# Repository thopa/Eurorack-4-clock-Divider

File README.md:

# Eurorack-4-clock-Divider
4 channel Eurorack Clock Divider, using Arduino NANO, and modified code from the Ardcore

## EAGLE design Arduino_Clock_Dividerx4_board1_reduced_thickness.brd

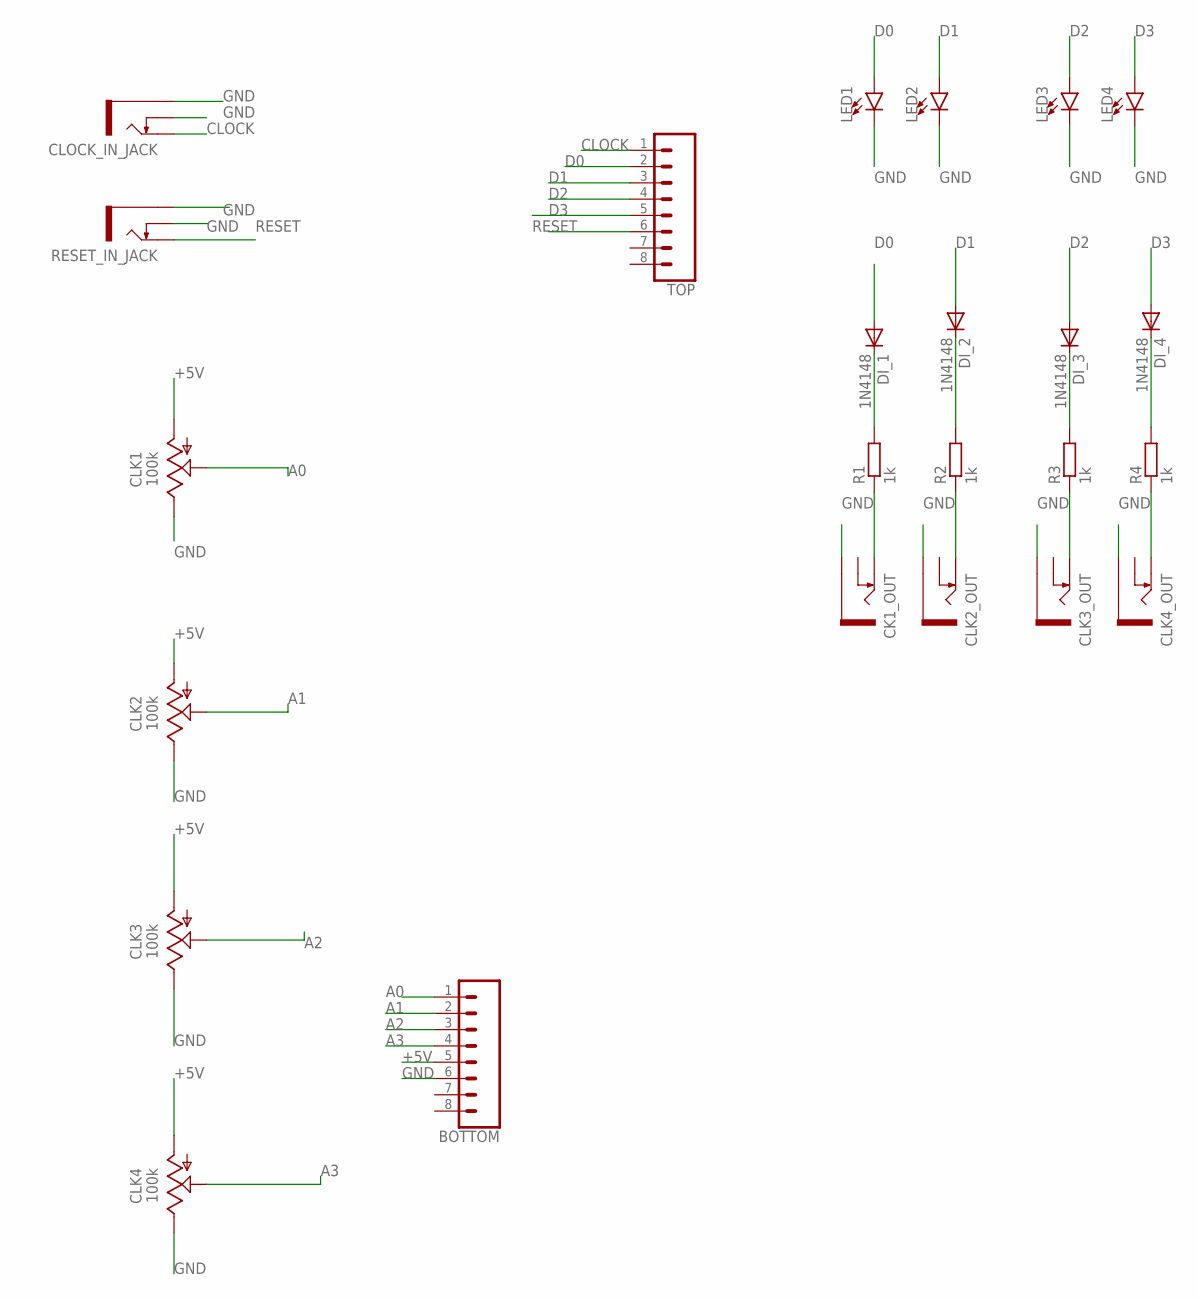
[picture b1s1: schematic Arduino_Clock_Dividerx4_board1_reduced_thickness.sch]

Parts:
BOTTOM: CONN_08LONGPADS; 1X08_LONGPADS
CK1_OUT: THONKICONNNEW; WQP-PJ301M-12_JACK
CLK1, CLK2, CLK3, CLK4: 100k; 9MM_SNAP-IN_POT
CLK2_OUT, CLK3_OUT, CLK4_OUT: THONKICONNNEW; WQP-PJ301M-12_JACK
CLOCK_IN_JACK: THONKICONNNEW; WQP-PJ301M-12_JACK
DI_1, DI_2, DI_3, DI_4: 1N4148; DO35-7
LED1, LED2, LED3, LED4: LED3MM; LED_3MM
R1, R2, R3, R4: 1k; 7MM_RESISTOR
RESET_IN_JACK: THONKICONNNEW; WQP-PJ301M-12_JACK
TOP: CONN_08LONGPADS; 1X08_LONGPADS

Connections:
+5V: BOTTOM.5, CLK1.1 (A), CLK2.1 (A), CLK3.1 (A), CLK4.1 (A)
A0: BOTTOM.1, CLK1.2 (S)
A1: BOTTOM.2, CLK2.2 (S)
A2: BOTTOM.3, CLK3.2 (S)
A3: BOTTOM.4, CLK4.2 (S)
CLOCK: CLOCK_IN_JACK.P$1_TIP (TIP), TOP.1
D0: DI_1.A, LED1.A, TOP.2
D1: DI_2.A, LED2.A, TOP.3
D2: DI_3.A, LED3.A, TOP.4
D3: DI_4.A, LED4.A, TOP.5
DI2: DI_2.C, R2.2
GND: BOTTOM.6, CK1_OUT.P$3_SLEEVE (SLEEVE), CLK1.3 (E), CLK2.3 (E), CLK2_OUT.P$3_SLEEVE (SLEEVE), CLK3.3 (E), CLK3_OUT.P$3_SLEEVE (SLEEVE), CLK4.3 (E), CLK4_OUT.P$3_SLEEVE (SLEEVE), CLOCK_IN_JACK.P$2_SWITCH (SWITCH), CLOCK_IN_JACK.P$3_SLEEVE (SLEEVE), LED1.K (C), LED2.K (C), LED3.K (C), LED4.K (C), RESET_IN_JACK.P$2_SWITCH (SWITCH), RESET_IN_JACK.P$3_SLEEVE (SLEEVE)
unnamed: CLK3_OUT.P$1_TIP (TIP), R3.1
unnamed: CLK4_OUT.P$1_TIP (TIP), R4.1
unnamed: DI_1.C, R1.2
unnamed: DI_3.C, R3.2
unnamed: DI_4.C, R4.2
unnamed: CLK2_OUT.P$1_TIP (TIP), R2.1
unnamed: CK1_OUT.P$1_TIP (TIP), R1.1
RESET: RESET_IN_JACK.P$1_TIP (TIP), TOP.6

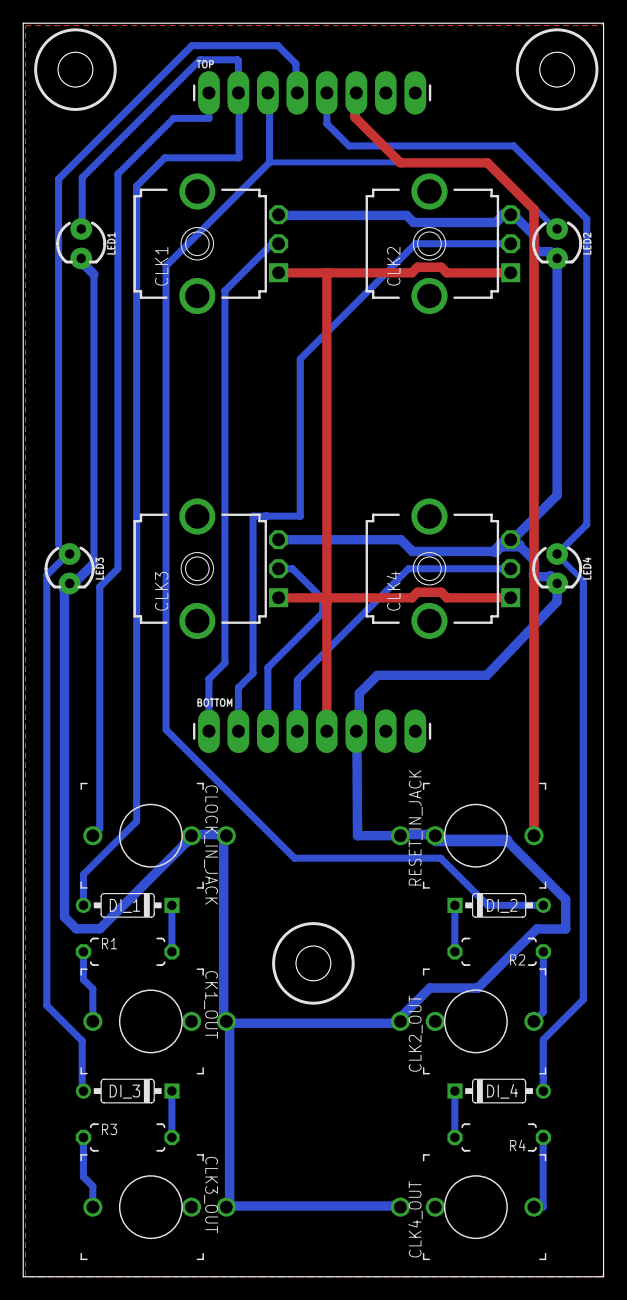
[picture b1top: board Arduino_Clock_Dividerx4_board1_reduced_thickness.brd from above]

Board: 2 copper layers, 50.0 x 108.0 mm, 27 parts (0 on the bottom side), 20 nets.

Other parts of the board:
H1, H2, H3: DRIL-3

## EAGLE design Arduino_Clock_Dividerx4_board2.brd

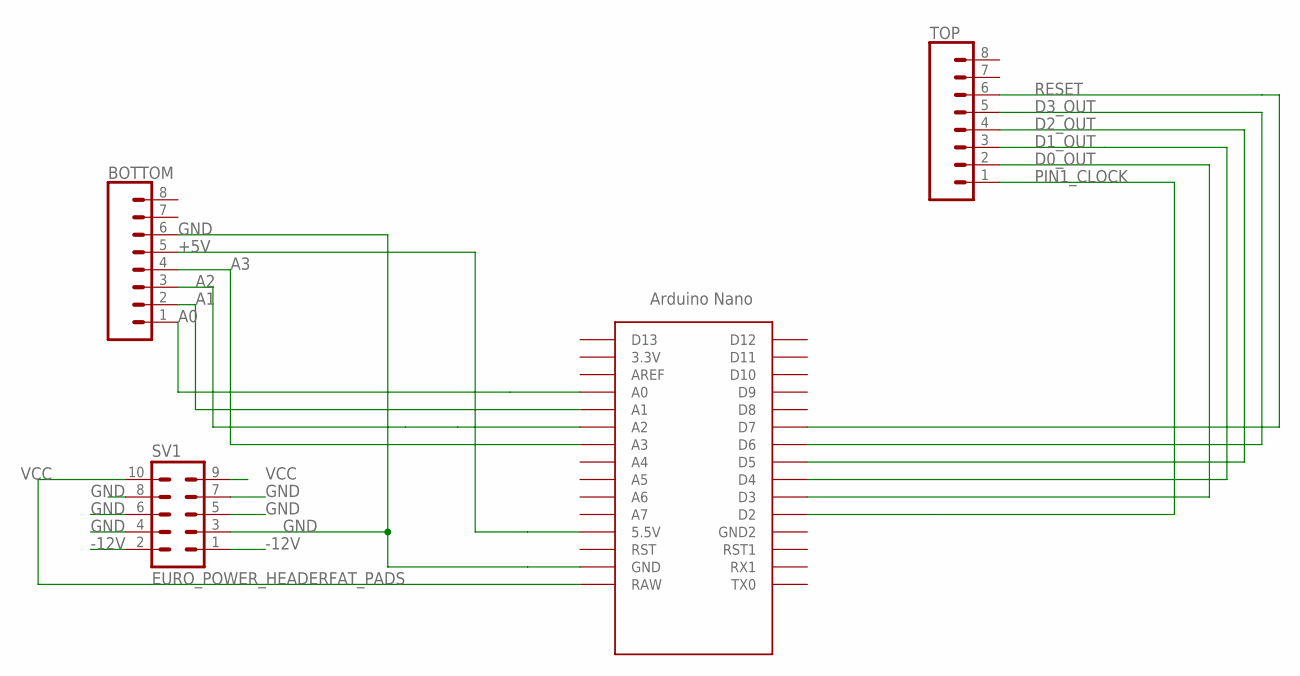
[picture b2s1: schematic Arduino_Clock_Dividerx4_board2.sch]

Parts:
BOTTOM: CONN_08LONGPADS; 1X08_LONGPADS
SV1: EURO_POWER_HEADERFAT_PADS; EURO_PWR_HEADER_FAT
TOP: CONN_08LONGPADS; 1X08_LONGPADS
U$1: NANO

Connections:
+5V: BOTTOM.5, U$1.5V (5.5V)
-12V: SV1.1, SV1.2
A0: BOTTOM.1, U$1.A0
A1: BOTTOM.2, U$1.A1
A2: BOTTOM.3, U$1.A2
A3: BOTTOM.4, U$1.A3
D0_OUT: TOP.2, U$1.D3
D1_OUT: TOP.3, U$1.D4
D2_OUT: TOP.4, U$1.D5
D3_OUT: TOP.5, U$1.D6
GND: BOTTOM.6, SV1.3, SV1.4, SV1.5, SV1.6, SV1.7, SV1.8, U$1.GND
PIN1_CLOCK: TOP.1, U$1.D2
RESET: TOP.6, U$1.D7
VCC: SV1.9, SV1.10, U$1.RAW

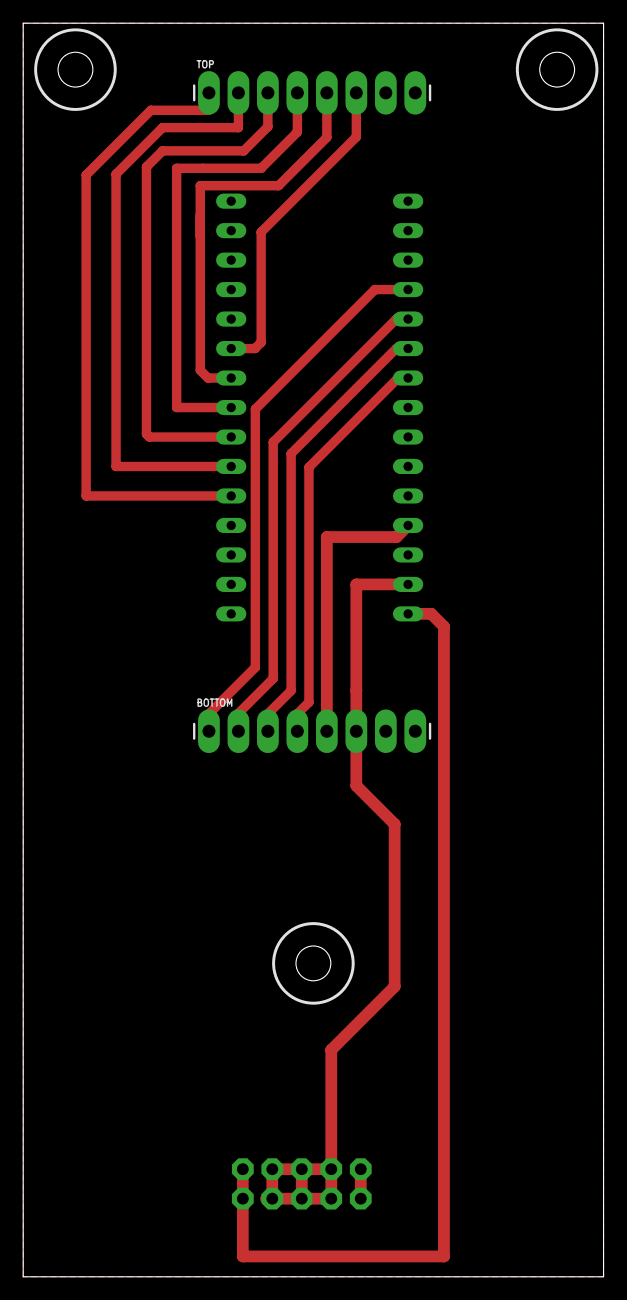
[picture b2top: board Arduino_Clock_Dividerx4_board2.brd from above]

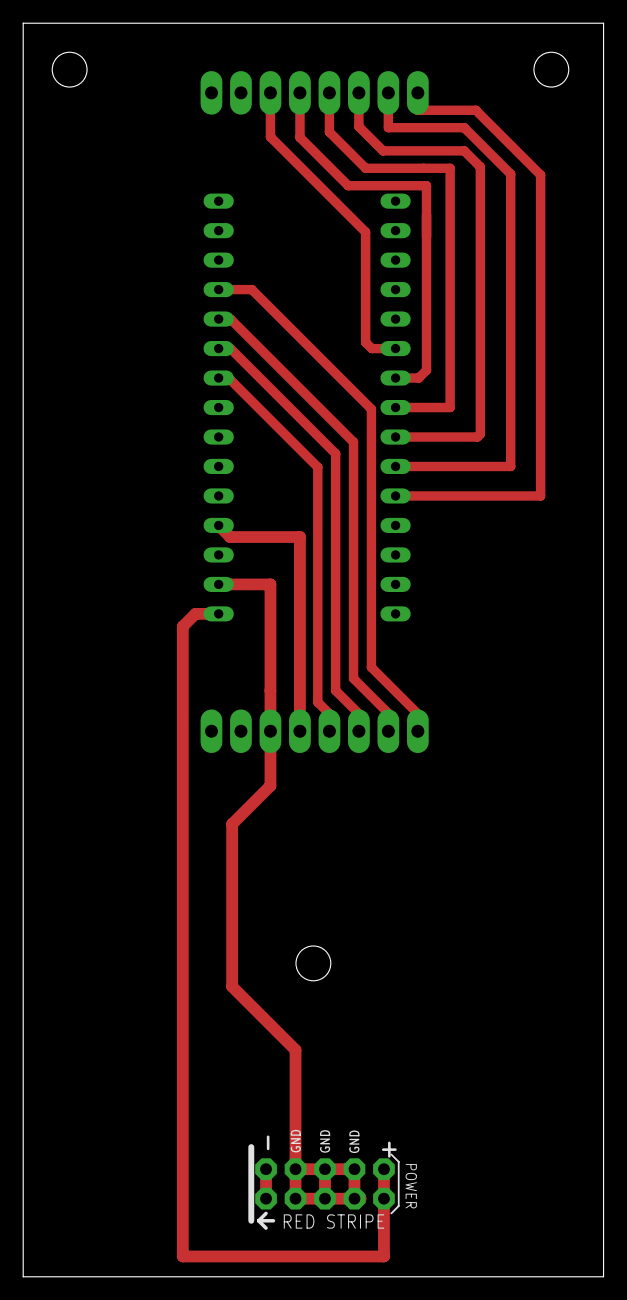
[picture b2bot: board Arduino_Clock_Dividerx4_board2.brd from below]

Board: 2 copper layers, 50.0 x 108.0 mm, 7 parts (2 on the bottom side), 14 nets.

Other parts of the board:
H1, H2, H4: DRIL-3

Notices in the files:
parts and their libraries:
SparkFun-LED: Licensing: Creative Commons ShareAlike 4.0 International - https://creativecommons.org/licenses/by-sa/4.0
